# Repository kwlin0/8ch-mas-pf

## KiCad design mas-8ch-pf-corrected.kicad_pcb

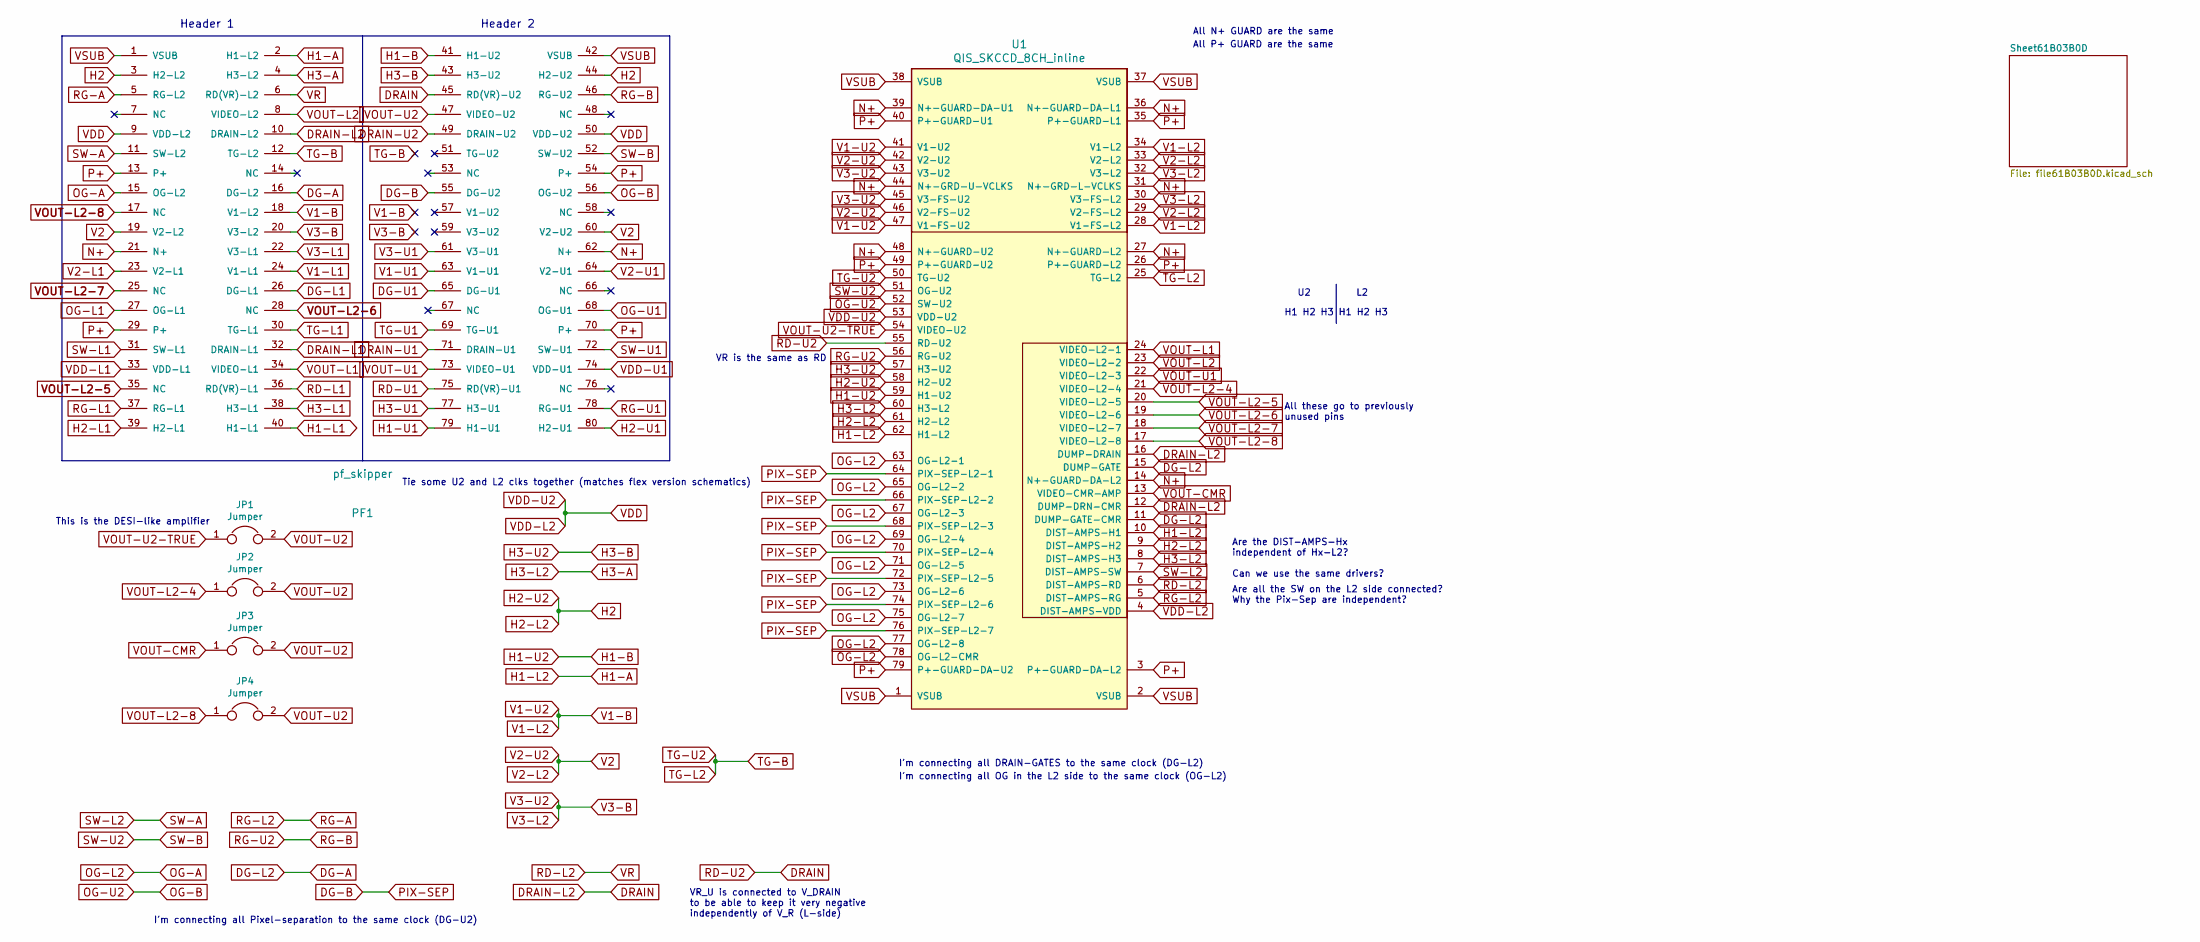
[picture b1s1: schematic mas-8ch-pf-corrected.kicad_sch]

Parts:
JP1, JP2, JP3, JP4: Jumper; PinHeader_1x02_P1.27mm_Vertical
PF1: pf_skipper
U1: QIS_SKCCD_8CH_inline; QIS_8ch_inline

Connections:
DG-A: PF1.16 (DG-L2), U1.11 (DUMP-GATE-CMR), U1.15 (DUMP-GATE)
DG-B: PF1.55 (DG-U2), U1.64 (PIX-SEP-L2-1), U1.66 (PIX-SEP-L2-2), U1.68 (PIX-SEP-L2-3), U1.70 (PIX-SEP-L2-4), U1.72 (PIX-SEP-L2-5), U1.74 (PIX-SEP-L2-6), U1.76 (PIX-SEP-L2-7)
DG-L1: PF1.26 (DG-L1)
DG-U1: PF1.65 (DG-U1)
DRAIN: PF1.10 (DRAIN-L2), PF1.45 (RD(VR)-U2), U1.12 (DUMP-DRN-CMR), U1.16 (DUMP-DRAIN), U1.55 (RD(VR)-U2)
DRAIN-L1: PF1.32 (DRAIN-L1)
DRAIN-U1: PF1.71 (DRAIN-U1)
DRAIN-U2: PF1.49 (DRAIN-U2)
H1-A: PF1.2 (H1-L2), U1.10 (DIST-AMPS-H1), U1.62 (H1-L2)
H1-B: PF1.41 (H1-U2), U1.59 (H1-U2)
H1-L1: PF1.40 (H1-L1)
H1-U1: PF1.79 (H1-U1)
H2: PF1.3 (H2-L2), PF1.44 (H2-U2), U1.9 (DIST-AMPS-H2), U1.58 (H2-U2), U1.61 (H2-L2)
H2-L1: PF1.39 (H2-L1)
H2-U1: PF1.80 (H2-U1)
H3-A: PF1.4 (H3-L2), U1.8 (DIST-AMPS-H3), U1.60 (H3-L2)
H3-B: PF1.43 (H3-U2), U1.57 (H3-U2)
H3-L1: PF1.38 (H3-L1)
H3-U1: PF1.77 (H3-U1)
N+: PF1.21 (N+), PF1.62 (N+), U1.14 (N+-GUARD-DA-L2), U1.27 (N+-GUARD-L2), U1.31 (N+-GRD-L-VCLKS), U1.36 (N+-GUARD-DA-L1), U1.39 (N+-GUARD-DA-U1), U1.44 (N+-GRD-U-VCLKS), U1.48 (N+-GUARD-U2)
OG-A: PF1.15 (OG-L2), U1.63 (OG-L2-1), U1.65 (OG-L2-2), U1.67 (OG-L2-3), U1.69 (OG-L2-4), U1.71 (OG-L2-5), U1.73 (OG-L2-6), U1.75 (OG-L2-7), U1.77 (OG-L2-8), U1.78 (OG-L2-CMR)
OG-B: PF1.56 (OG-U2), U1.52 (OG-U2)
OG-L1: PF1.27 (OG-L1)
OG-U1: PF1.68 (OG-U1)
P+: PF1.13 (P+), PF1.29 (P+), PF1.54 (P+), PF1.70 (P+), U1.3 (P+-GUARD-DA-L2), U1.26 (P+-GUARD-L2), U1.35 (P+-GUARD-L1), U1.40 (P+-GUARD-U1), U1.49 (P+-GUARD-U2), U1.79 (P+-GUARD-DA-U2)
RD-L1: PF1.36 (RD(VR)-L1)
RD-L2: PF1.6 (RD(VR)-L2), U1.6 (DIST-AMPS-RD(VR))
RD-U1: PF1.75 (RD(VR)-U1)
RG-A: PF1.5 (RG-L2), U1.5 (DIST-AMPS-RG)
RG-B: PF1.46 (RG-U2), U1.56 (RG-U2)
RG-L1: PF1.37 (RG-L1)
RG-U1: PF1.78 (RG-U1)
SW-A: PF1.11 (SW-L2), U1.7 (DIST-AMPS-SW)
SW-B: PF1.52 (SW-U2), U1.51 (SW-U2)
SW-L1: PF1.31 (SW-L1)
SW-U1: PF1.72 (SW-U1)
TG-B: PF1.12 (TG-L2), U1.25 (TG-L2), U1.50 (TG-U2)
TG-L1: PF1.30 (TG-L1)
TG-U1: PF1.69 (TG-U1)
V1-B: PF1.18 (V1-L2), U1.28 (V1-FS-L2), U1.34 (V1-L2), U1.41 (V1-U2), U1.47 (V1-FS-U2)
V1-L1: PF1.24 (V1-L1)
V1-U1: PF1.63 (V1-U1)
V2: PF1.19 (V2-L2), PF1.60 (V2-U2), U1.29 (V2-FS-L2), U1.33 (V2-L2), U1.42 (V2-U2), U1.46 (V2-FS-U2)
V2-L1: PF1.23 (V2-L1)
V2-U1: PF1.64 (V2-U1)
V3-B: PF1.20 (V3-L2), U1.30 (V3-FS-L2), U1.32 (V3-L2), U1.43 (V3-U2), U1.45 (V3-FS-U2)
V3-L1: PF1.22 (V3-L1)
V3-U1: PF1.61 (V3-U1)
VDD: PF1.9 (VDD-L2), PF1.50 (VDD-U2), U1.4 (DIST-AMPS-VDD), U1.53 (VDD-U2)
VDD-L1: PF1.33 (VDD-L1)
VDD-U1: PF1.74 (VDD-U1)
VOUT-CMR: JP3.1, U1.13 (VIDEO-CMR-AMP)
VOUT-L1: PF1.34 (VIDEO-L1), U1.24 (VIDEO-L2-1)
VOUT-L2: PF1.8 (VIDEO-L2), U1.23 (VIDEO-L2-2)
VOUT-L2-4: JP2.1, U1.21 (VIDEO-L2-4)
VOUT-L2-5: PF1.35 (NC), U1.20 (VIDEO-L2-5)
VOUT-L2-6: PF1.28 (NC), U1.19 (VIDEO-L2-6)
VOUT-L2-7: PF1.25 (NC), U1.18 (VIDEO-L2-7)
VOUT-L2-8: JP4.1, PF1.17 (NC), U1.17 (VIDEO-L2-8)
VOUT-U1: PF1.73 (VIDEO-U1), U1.22 (VIDEO-L2-3)
VOUT-U2: JP1.2, JP2.2, JP3.2, JP4.2, PF1.47 (VIDEO-U2)
VOUT-U2-TRUE: JP1.1, U1.54 (VIDEO-U2)
VSUB: PF1.1 (VSUB), PF1.42 (VSUB), U1.1 (VSUB), U1.2 (VSUB), U1.37 (VSUB), U1.38 (VSUB)

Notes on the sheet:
Are all the SW on the L2 side connected? Why the Pix-Sep are independent?
Header 2
Header 1
Are the DIST-AMPS-Hx independent of Hx-L2? Can we use the same drivers?
VR_U is connected to V_DRAIN to be able to keep it very negative independently of V_R (L-side)
All N+ GUARD are the same
I'm connecting all DRAIN-GATES to the same clock (DG-L2)
I'm connecting all Pixel-separation to the same clock (DG-U2)
All P+ GUARD are the same
H1 H2 H3 H1 H2 H3
I'm connecting all OG in the L2 side to the same clock (OG-L2)
Tie some U2 and L2 clks together (matches flex version schematics)
This is the DESI-like amplifier
VR is the same as RD
All these go to previously unused pins

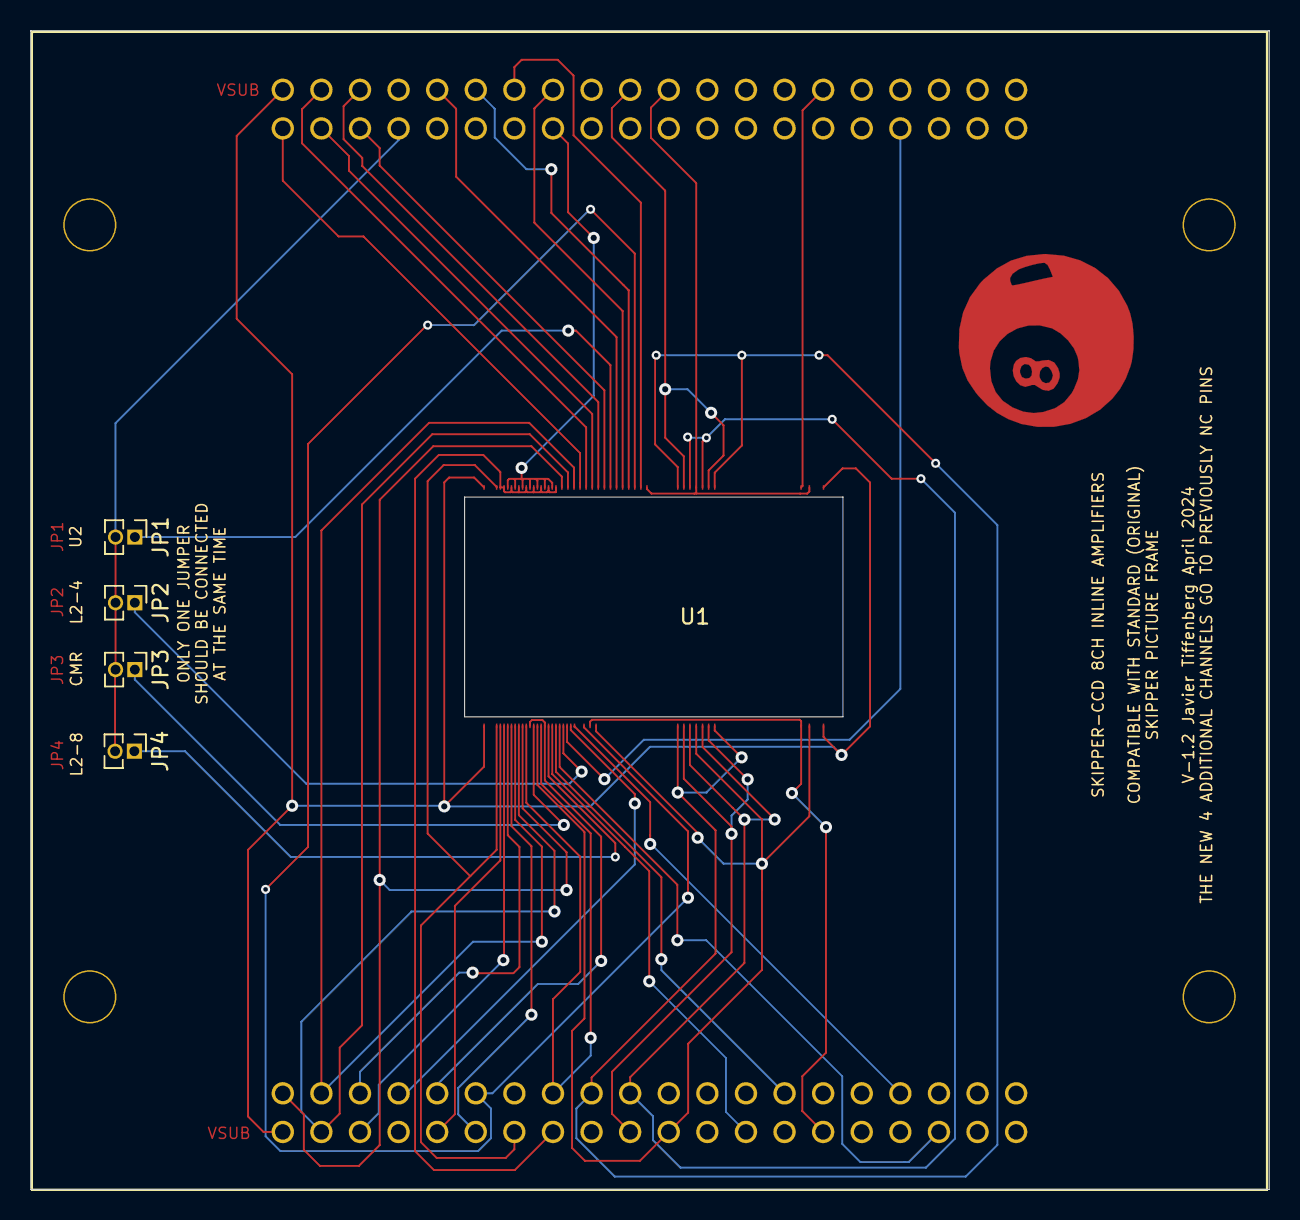
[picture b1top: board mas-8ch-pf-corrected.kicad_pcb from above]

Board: 2 copper layers, 81.5 x 76.2 mm, 6 parts (0 on the bottom side), 34 nets.
